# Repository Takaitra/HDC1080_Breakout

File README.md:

# HDC1080 Breakout Board

This is a breadboard-friendly breakout board for the HDC1080 Humidity/Temperature sensor. This repository contains the Eagle design files. You will also need to install the [Takaitra Eagle library](https://github.com/Takaitra/Takaitra-Eagle-Libraries).

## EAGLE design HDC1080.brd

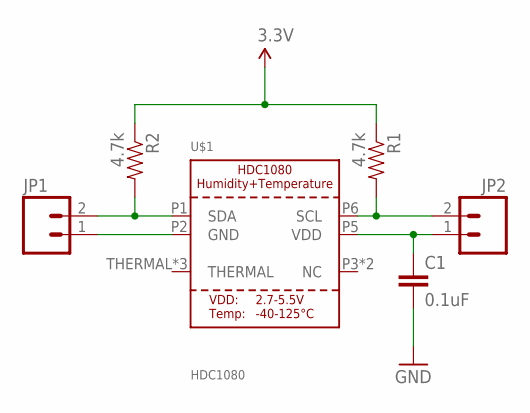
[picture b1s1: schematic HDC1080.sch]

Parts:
C1: 0.1uF; 0603-CAP
JP1, JP2: M02PTH; 1X02
R1, R2: 4.7k; 0805
U$1: HDC1080; PWSON-6

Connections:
3.3V: C1.1, JP2.1, R1.1, R2.1, U$1.P5 (VDD)
GND: C1.2, JP1.1, U$1.P2 (GND)
SCL: JP2.2, R1.2, U$1.P6 (SCL)
SDA: JP1.2, R2.2, U$1.P1 (SDA)

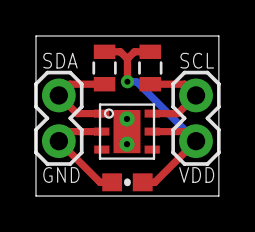
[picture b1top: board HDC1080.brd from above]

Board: 2 copper layers, 10.2 x 8.9 mm, 6 parts (0 on the bottom side), 4 nets.

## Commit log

2018-10-25 Add Eagle files and README

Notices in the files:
parts and their libraries:
SparkFun-Connectors: Licensing: Creative Commons ShareAlike 4.0 International - https://creativecommons.org/licenses/by-sa/4.0
